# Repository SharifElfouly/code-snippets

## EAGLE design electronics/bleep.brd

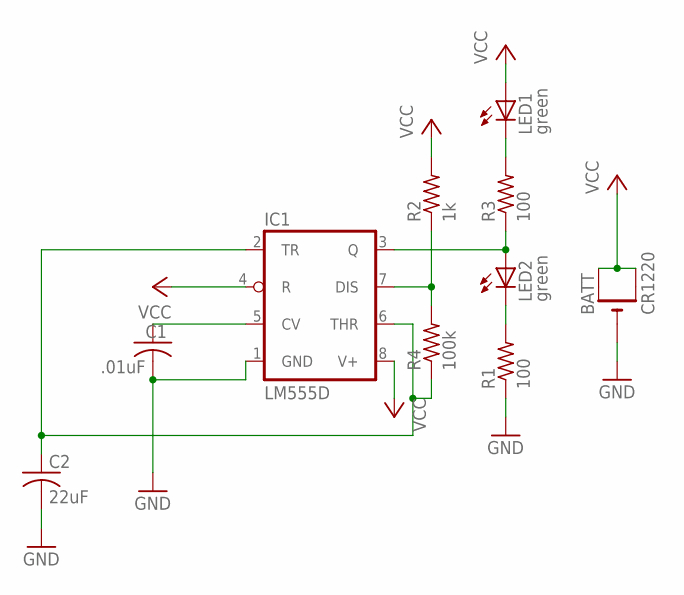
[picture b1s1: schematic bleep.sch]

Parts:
BATT: CR1220; CR1220-SMD
C1: .01uF; C0805
C2: 22uF; C0805
IC1: LM555D; SO08
LED1, LED2: green; CHIPLED_0805
R1, R3: 100; R0805
R2: 1k; R0805
R4: 100k; R0805

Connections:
GND: BATT.-, C1.2, C2.2, IC1.1 (GND), R1.1
unnamed: IC1.7 (DIS), R2.1, R4.2
unnamed: LED1.C, R3.2
unnamed: IC1.3 (Q), LED2.A, R3.1
unnamed: LED2.C, R1.2
unnamed: C2.1, IC1.2 (TR), IC1.6 (THR), R4.1
unnamed: C1.1, IC1.5 (CV)
VCC: BATT.+$1 (+), BATT.+$2 (+1), IC1.4 (R), IC1.8 (V+), LED1.A, R2.2

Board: 2 copper layers, 10 parts (0 on the bottom side), 8 nets, no tracks yet.

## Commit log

2020-01-10 tf is such a mess
2020-01-14 Create install-nvidia.md
    nvidia-drivers and nvidia-docker installation manual for Ubuntu 18.04
2020-01-16 enocde and decode a binary mask with the cocoapi
2020-01-16 decode string byte rle encoded mask
2020-01-16 run onnx mask r-cnn
2020-01-16 deleted env
2020-01-16 run Detectron Mask R-CNN
2020-01-16 model loads
2020-01-16 detectron2 runs
2020-01-17 simple inference with tflite
2020-01-17 rm .devconatiner
2020-01-17 bbox pred thermal
2020-01-17 removed devcontainer
2020-02-11 not writing this again
2020-02-18 frames-to-video
2020-02-26 size of mask encodings with cocoapi
2020-05-28 Run DETR via PyTorch Hub
2020-06-02 Create AdelaiDet-docker
2020-06-05 panoptic nice
2020-06-10 simple resizing works
2020-06-10 works dynamically
2020-06-10 demo works
2020-06-10 dewarp
2020-06-11 added comments
2020-06-13 run yolov3
2020-06-17 apply to dir
2020-06-17 os is a mess
2020-06-19 190ms
2020-06-20 timeit
2020-06-20 Create detecoRS-dockerfile
2020-06-23 parallel stuff
2020-06-27 libs and readme.md
2020-06-27 designing pcb
2020-06-29 classification
2020-07-05 seems cool but is expensive
2020-07-26 dirly broken
2020-08-04 api and stuff
2020-08-05 filter
2020-08-19 I want standalone Keras back
2020-08-19 extract bbox
2020-09-02 mask on image
2020-09-02 add mask to image
2020-09-05 works 20%
2020-10-24 detect faces and calc embeddings
2020-10-26 nice
2020-10-29 lstm
2020-10-30 cnn + lstm + linear
2020-11-02 check if video not dir
2020-11-02 note to self
2020-11-03 random eda
2020-11-03 comp link
2020-11-04 subplots
2020-11-11 conv_grad
2020-11-11 bn grad
2020-11-14 loss/pool grad
2020-11-15 seq to seq
2020-11-18 transforms
2020-11-19 sgd+mom
2020-11-24 stonks
2020-12-03 optim
